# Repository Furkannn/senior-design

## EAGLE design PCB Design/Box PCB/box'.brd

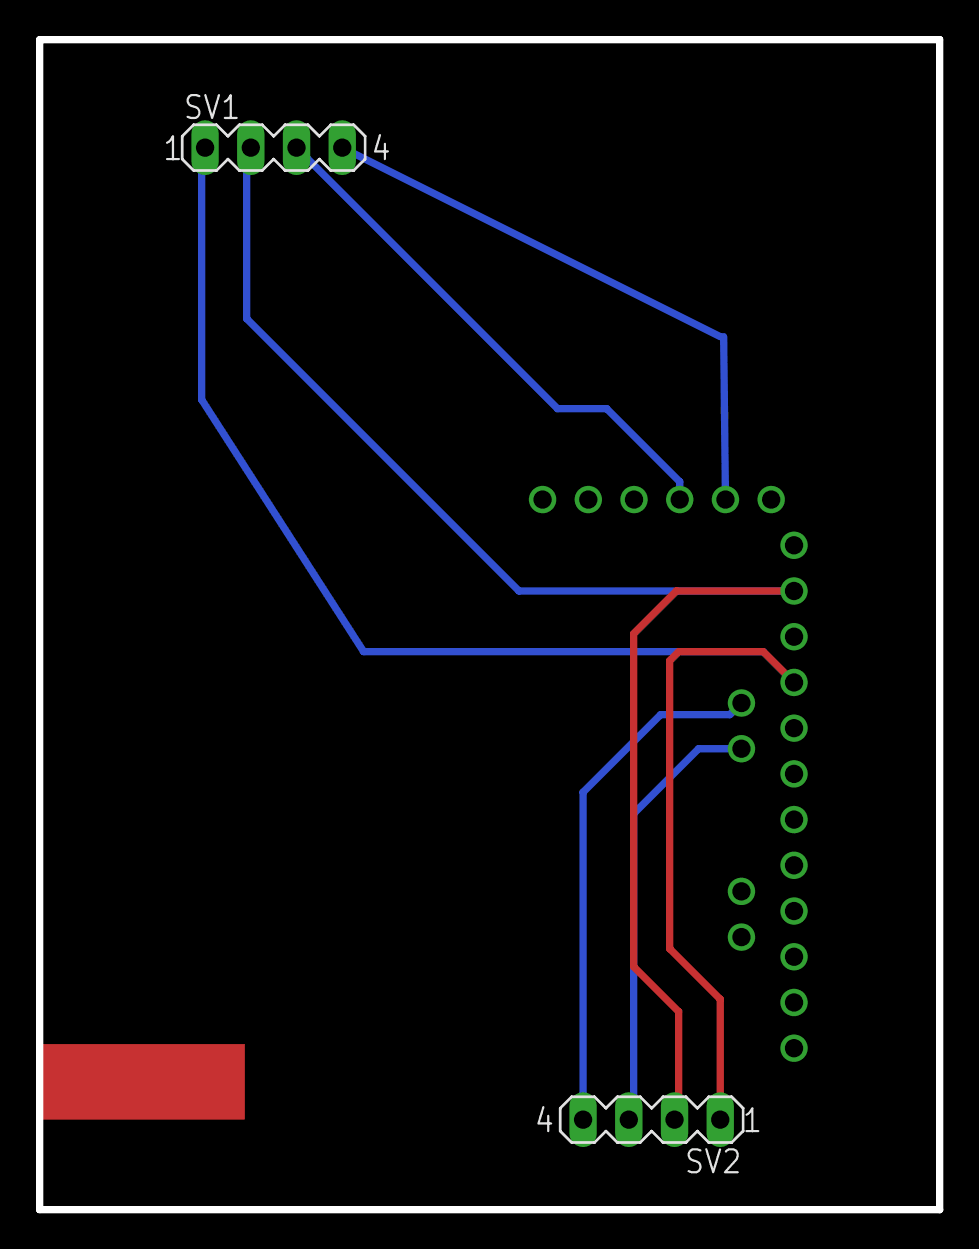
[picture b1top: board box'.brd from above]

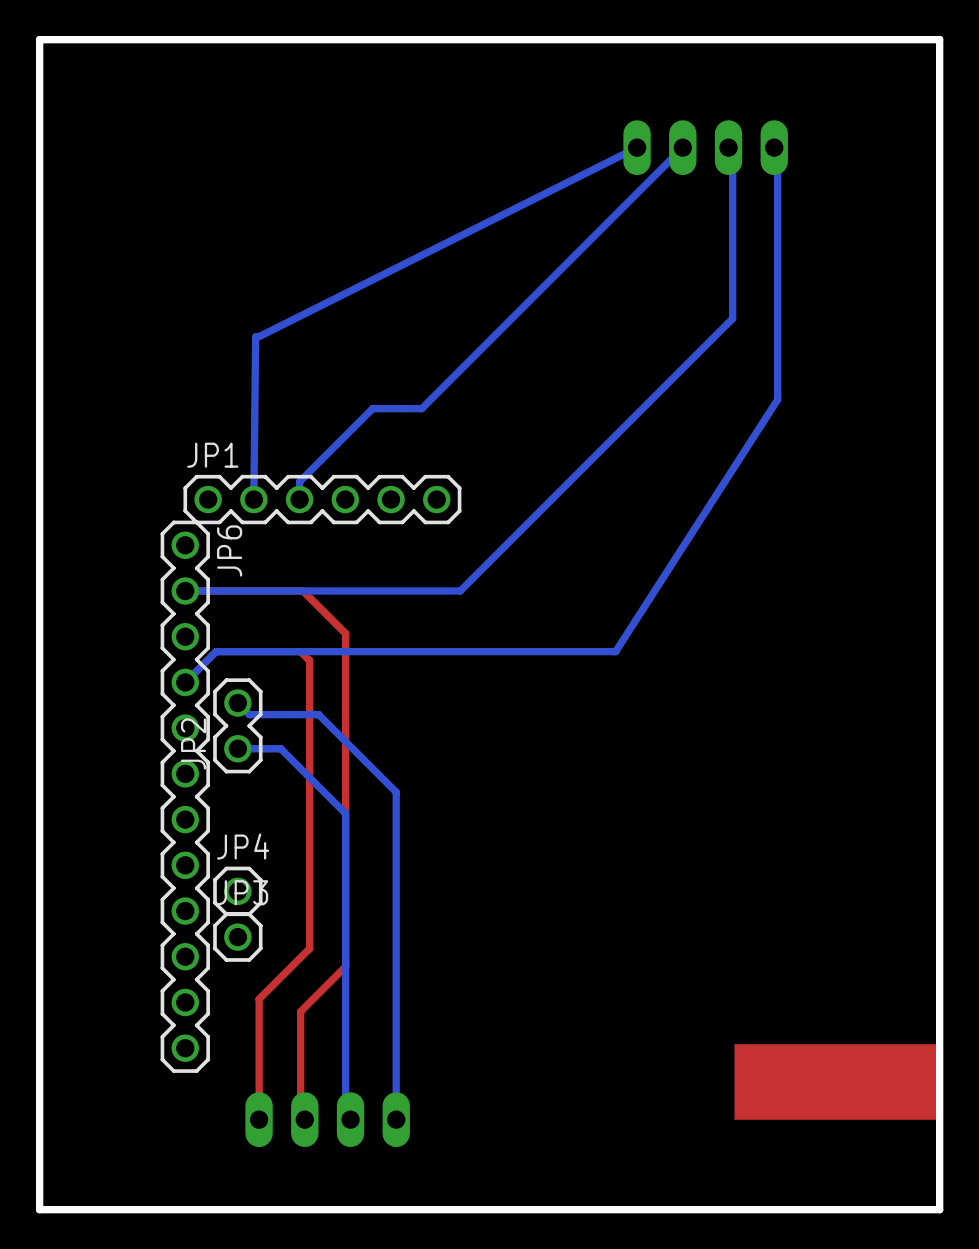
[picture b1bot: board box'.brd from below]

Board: 2 copper layers, 50.0 x 65.0 mm, 7 parts (5 on the bottom side), 5 nets.

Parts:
JP1: FTDI Basic; 1X06
JP2: 1X02
JP3, JP4: 1X01
JP6: 1X12
SV1, SV2: MA04-1

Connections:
S$2: JP1.3, SV1.3
S$3: JP2.2, SV2.4
S$4: JP2.1, SV2.3
S$5: JP6.2, SV1.2, SV2.2
S$6: JP6.4, SV1.1, SV2.1

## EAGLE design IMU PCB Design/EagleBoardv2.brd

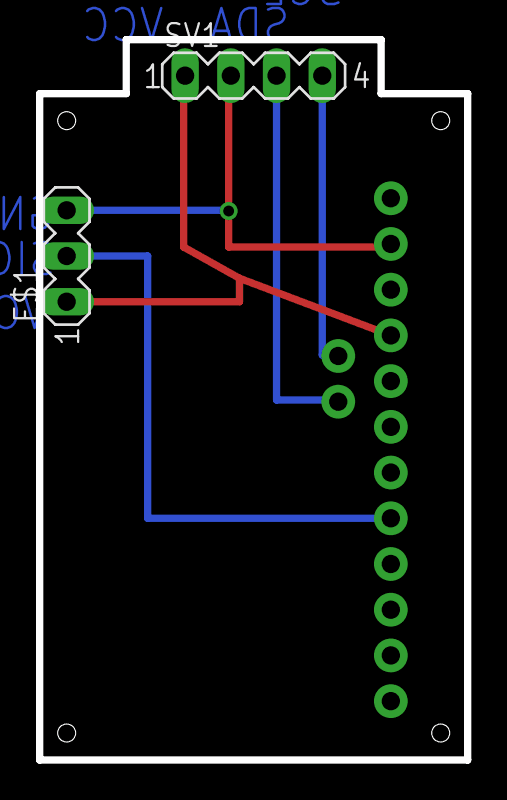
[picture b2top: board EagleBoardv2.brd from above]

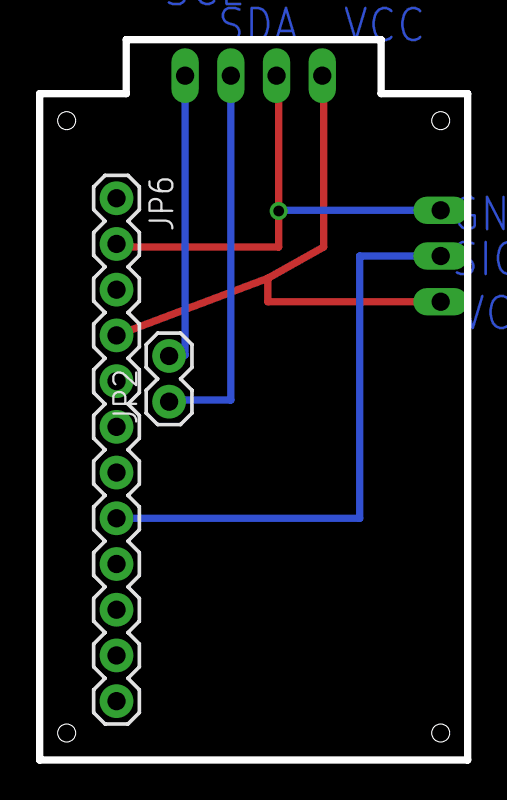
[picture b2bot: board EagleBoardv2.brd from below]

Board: 2 copper layers, 23.8 x 40.0 mm, 4 parts (2 on the bottom side), 5 nets.

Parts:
E$1: MA03-1
JP2: 1X02
JP6: 1X12
SV1: MA04-1

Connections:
S$2: JP2.1, SV1.3
S$3: JP2.2, SV1.4
S$4: E$1.1, JP6.4, SV1.1
S$5: E$1.2, JP6.8
S$6: E$1.3, JP6.2, SV1.2

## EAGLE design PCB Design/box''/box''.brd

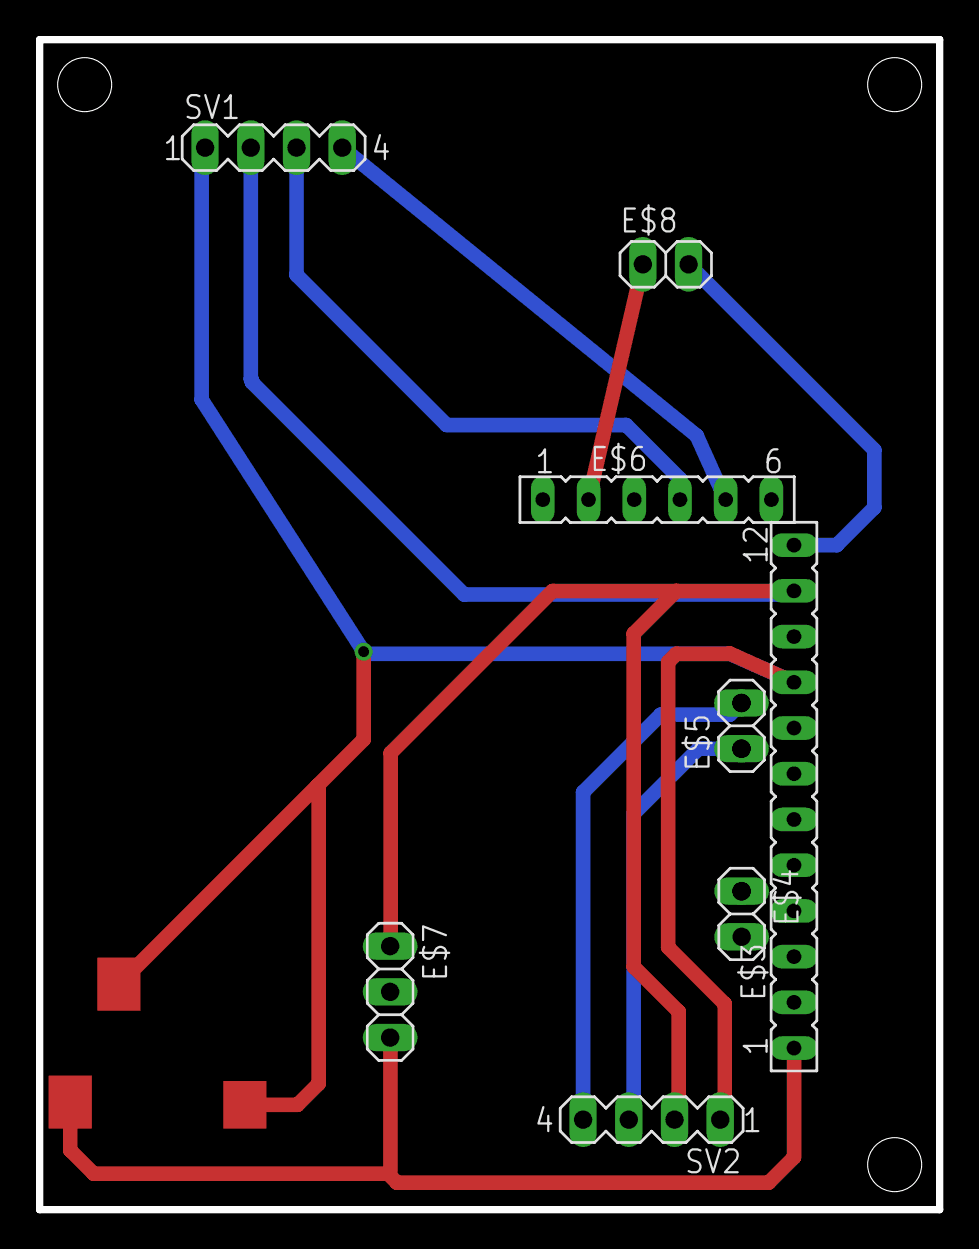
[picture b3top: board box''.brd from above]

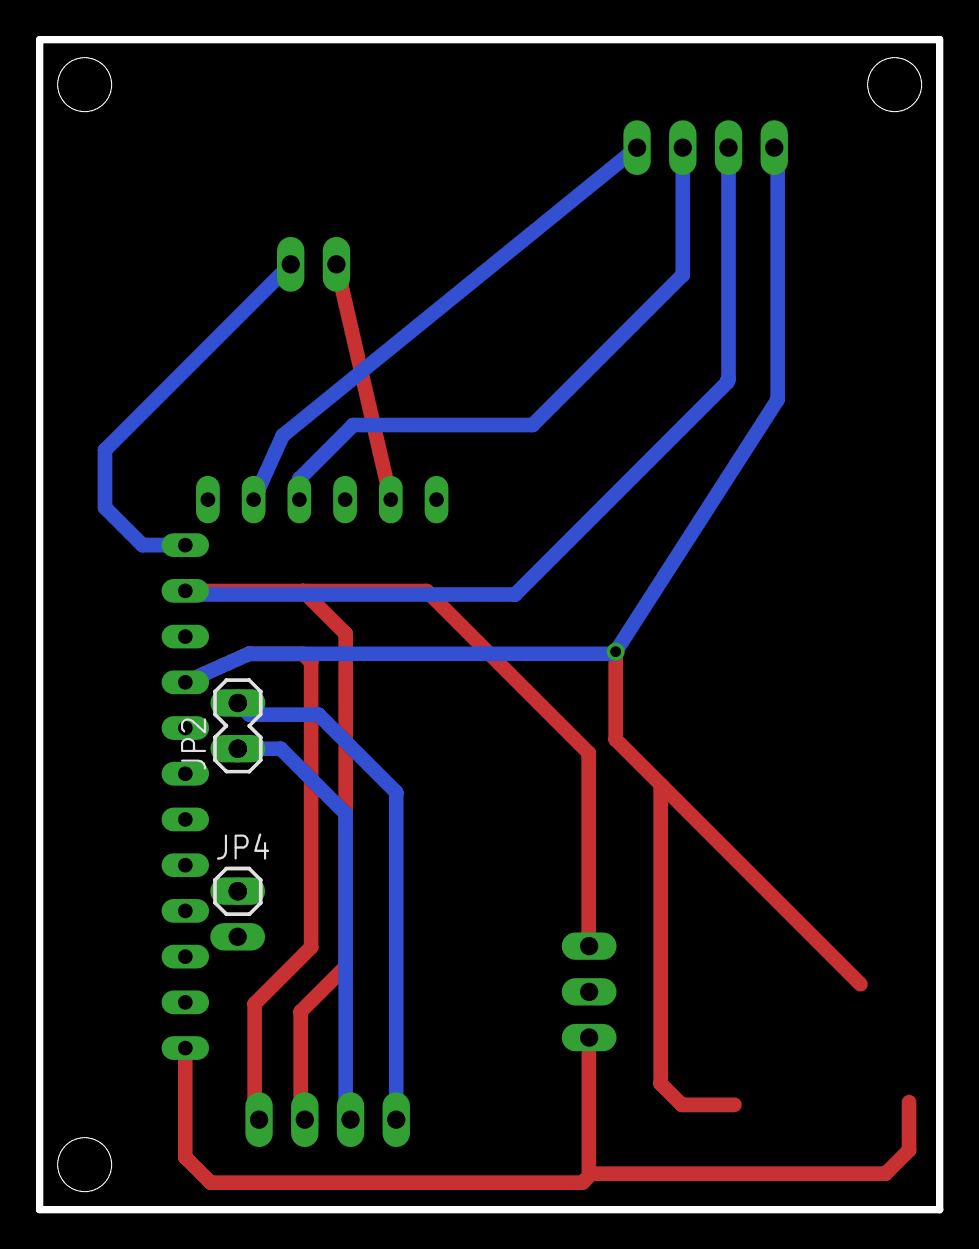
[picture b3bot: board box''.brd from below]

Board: 2 copper layers, 50.0 x 65.0 mm, 11 parts (2 on the bottom side), 7 nets.

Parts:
E$1: SMDAUDIO
E$3: FE12
E$4, E$5, E$8: 1X02
E$6: FE06
E$7: 1X03
JP2: 1X02
JP4: 1X01
SV1, SV2: MA04-1

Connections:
S$2: E$6.4, SV1.3
S$3: JP2.2, SV2.4
S$4: JP2.1, SV2.3
S$5: E$3.11, SV1.2, SV2.2
S$6: E$1.P$2, E$1.P$3, E$3.9, SV1.1, SV2.1
S$9: E$6.2, E$8.1
S$11: E$3.12, E$8.2

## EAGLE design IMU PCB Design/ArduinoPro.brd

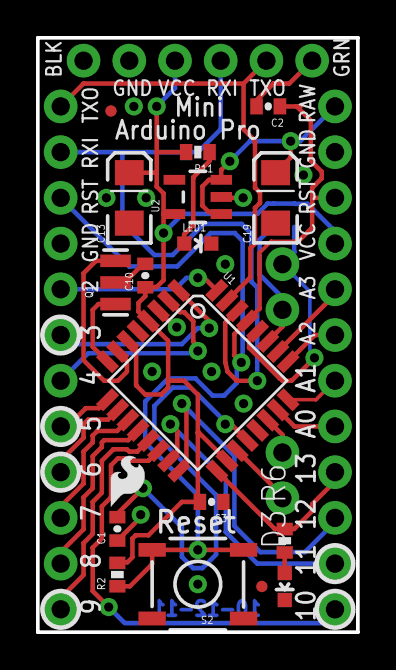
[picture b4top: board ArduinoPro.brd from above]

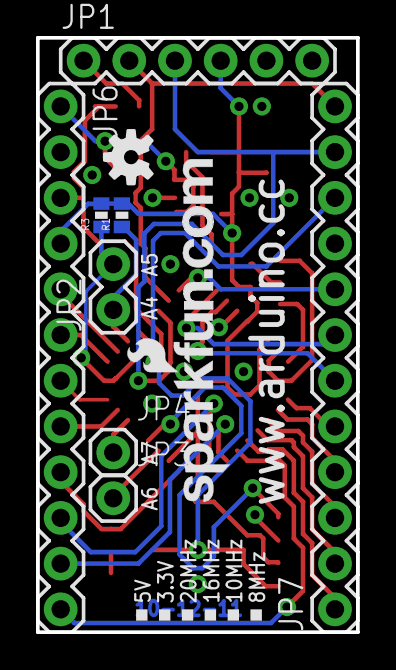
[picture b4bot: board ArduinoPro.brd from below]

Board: 2 copper layers, 17.8 x 33.0 mm, 28 parts (10 on the bottom side), 32 nets.

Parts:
C1, C2, C3, C10: 0.1uF; 0402-CAP
C13, C19: 10uF; EIA3216
D3: Green; LED-0603
JP1: FTDI Basic; 1X06
JP2: 1X02
JP3, JP4: 1X01
JP5, JP8: FIDUCIALUFIDUCIAL; MICRO-FIDUCIAL
JP6, JP7: 1X12
LED1: Red; LED-0603
Q1: 8/16/20MHz; RESONATOR-SMD
R1, R3: 0402-RES
R2, R11: 10K; 0402-RES
R6: 330; 0402-RES
S2: Reset; TACTILE_SWITCH_SMD
U1: ATMEGA328; TQFP32-08
U2: MIC5205; SOT23-5
U$1: LOGO-SFESK; SFE-LOGO-FLAME
U$3: OSHW-LOGOS; OSHW-LOGO-S
U$11: LOGO-SFENEW; SFE-NEW-WEBLOGO

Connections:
A0: JP6.8, U1.23
A1: JP6.7, U1.24
A2: JP6.6, U1.25
A3: JP6.5, U1.26
A4: JP2.1, R1.1, U1.27
A5: JP2.2, R3.1, U1.28
A6: JP3.1, U1.19
A7: JP4.1, U1.22
AREF: C1.2, U1.20
D2: JP7.8, U1.32
D3: JP7.7, U1.1
D4: JP7.6, U1.2
D5: JP7.5, U1.9
D6: JP7.4, U1.10
D7: JP7.3, U1.11
D8: JP7.2, U1.12
D9: JP7.1, U1.13
D10: JP6.12, U1.14
DTR: C2.2, JP1.1
GND: C1.1, C3.1, C10.2, C13.C, C19.C, D3.C, JP1.5, JP1.6, JP6.2, JP7.9, LED1.C, Q1.2, S2.1, S2.2, U1.3, U1.5, U1.21, U2.2
MISO: JP6.10, U1.16
MOSI: JP6.11, U1.15
unnamed: Q1.1, U1.8
unnamed: Q1.3, U1.7
unnamed: D3.A, R6.2
unnamed: LED1.A, R11.1
RAW: C19.A, JP6.1, U2.1, U2.3
RESET: C2.1, JP6.3, JP7.10, R2.1, S2.3, S2.4, U1.29
RXI: JP1.3, JP7.11, U1.30
SCK: JP6.9, R6.1, U1.17
TXO: JP1.2, JP7.12, U1.31
VCC: C3.2, C10.1, C13.A, JP1.4, JP6.4, R1.2, R2.2, R3.2, R11.2, U1.4, U1.6, U1.18, U2.5

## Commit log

2013-03-24 initial commit and python IMUSerial module completed
2013-03-24 serial and imu class complete
2013-03-24 now updating neutral position
2013-03-24 read and update parameters from file
2013-03-24 move cursor implemented but moves very rapidly
2013-03-25 working. still need to implement neutralzone and optimized neutral position
2013-03-25 neutral zone implemented
2013-03-25 trivial
2013-03-25 implemented optimized neutral position
2013-03-25 added move state
2013-03-26 removing pyc
2013-03-26 solidworks files
2013-03-26 cleanup
2013-03-31 working prototype of nod detection
2013-03-31 improved yaml handling
2013-04-01 fixed record training data file
2013-04-01 changed recorder and formatter into classes
2013-04-02 completed train model convertion into class
2013-04-03 working gesture recog
2013-04-04 before intergrating fsm with pca
2013-04-04 added click code and LOTS of OOP cleanup
2013-04-06 trying to fix sudden bursts
2013-04-09 before restructuring mouse control code
2013-04-09 created joystick and dynamic_neutral mode
2013-04-09 added log based optimized neutral point
2013-04-10 schematic and gui changes
2013-04-10 ignore pyc
2013-04-14 clicking working
2013-04-14 UI changes reflected in software
2013-04-16 added message capability
2013-04-18 status and recenter flags added
2013-04-18 fixed termination conditions
2013-04-18 detecting shakes
2013-04-19 project summary and changed ui to remove left and right buttons
2013-04-19 before changing main code to integrate gesture recog
2013-04-19 shakes now recenter
2013-04-20 preparing to record shake data
2013-04-21 added calibrate flag
2013-04-21 configured train button and added messages
2013-04-21 changed update time for message
2013-04-22 try catch in the read message
2013-04-23 now checks for bluetooth devices and works at 9600 baudrate
2013-04-25 non python related files
2013-04-25 just tested with and without bluetooth. this shit worksgit statusgit status! Expo ETA - 3 hrs
